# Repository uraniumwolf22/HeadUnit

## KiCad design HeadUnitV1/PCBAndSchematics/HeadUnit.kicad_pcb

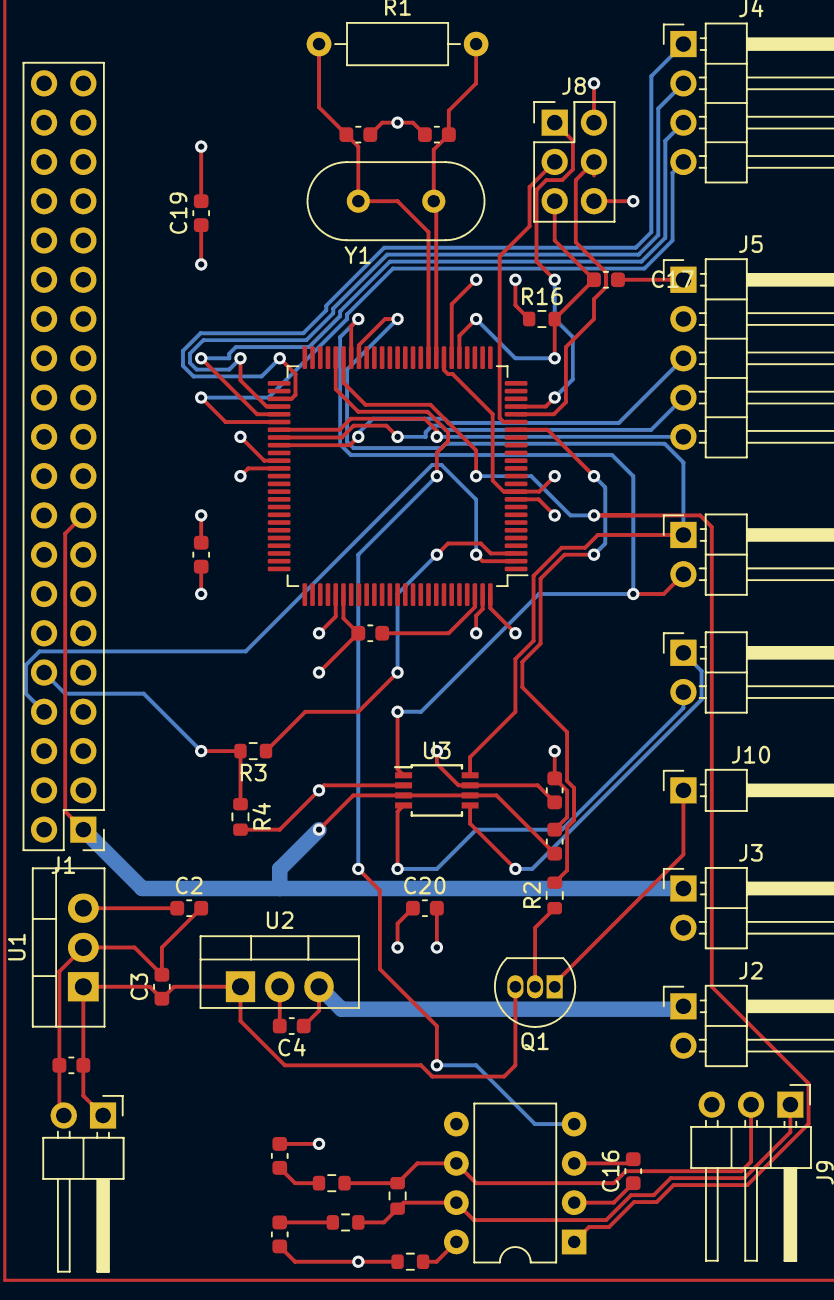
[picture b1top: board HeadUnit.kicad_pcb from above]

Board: 4 copper layers, 43 parts (0 on the bottom side), 36 nets.

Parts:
C1, C3: 0.33uF; C_0603_1608Metric
C2, C4, C5, C6, C16, C17: 0.1uF; C_0603_1608Metric
C9, C10: 22pf; C_0603_1608Metric
C14, C15: 560pF; C_0603_1608Metric
C18, C19, C20, C21: 0.1uf; C_0603_1608Metric
J1: Raspberry_Pi_2_3; PinHeader_2x20_P2.54mm_Vertical
J2: 5VOUT; PinHeader_1x02_P2.54mm_Horizontal
J3: 3V3OUT; PinHeader_1x02_P2.54mm_Horizontal
J4: MC_GPIO; PinHeader_1x04_P2.54mm_Horizontal
J5: ENC_CONN; PinHeader_1x05_P2.54mm_Horizontal
J6: I2C_LV; PinHeader_1x02_P2.54mm_Horizontal
J7: I2C_HV; PinHeader_1x02_P2.54mm_Horizontal
J8: AVR-ISP-6; PinHeader_2x03_P2.54mm_Vertical
J9: CAN_CONN; PinHeader_1x03_P2.54mm_Horizontal
J10: amp Conn; PinHeader_1x01_P2.54mm_Horizontal
J11: Conn_01x02_Pin; PinHeader_1x02_P2.54mm_Horizontal
Q1: 2N3904; TO-92_Inline
R1: 1M; R_Axial_DIN0207_L6.3mm_D2.5mm_P10.16mm_Horizontal
R2: 220; R_0603_1608Metric
R3: 510ohm; R_0603_1608Metric
R4: 1k; R_0603_1608Metric
R12: 120E; R_0603_1608Metric
R13, R14: 100E; R_0603_1608Metric
R15, R16: 4.7k; R_0603_1608Metric
U1, U2: LM7805_TO220; TO-220-3_Vertical
U3: TCA9406DC; TSSOP-8_3x3mm_P0.65mm
U5: MCP2551-I-P; DIP-8_W7.62mm
U6: ATmega2560-16A; TQFP-100_14x14mm_P0.5mm
Y1: 8Mhz; Crystal_HC49-4H_Vertical

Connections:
+3.3V: C5.1, J1.1 (3V3), J1.17 (3V3), J3.1, U3.3 (VCCA), U3.6 (OE)
+5V: C2.1, C6.2, C16.2, C19.2, C20.2, C21.2, J1.2 (5V), J1.4 (5V), J5.2, J8.2 (VCC), R16.1, U1.3 (VO), U3.7 (VCCB), U5.3 (VDD), U6.10 (VCC), U6.31 (VCC), U6.61 (VCC), U6.80 (VCC), U6.100 (AVCC)
+12V: C1.1, C3.1, J11.1, Q1.3 (C), U1.1 (VI), U2.1 (VI)
/5v_AUX: C4.1, J2.1, U2.3 (VO)
/AMP_CTRL: R2.2, U6.19 (PB0)
/AMP_SIG: J10.1, Q1.1 (E)
/CAN_H: J9.1, R12.1, R14.1, U5.7 (CANH)
/CAN_L: J9.2, R12.2, R13.1, U5.6 (CANL)
/CAN_RX: U5.1 (TXD), U6.45 (PD2)
/CAN_TX: U5.4 (RXD), U6.46 (PD3)
/ENC_CLK: J5.5, U6.57 (PC4)
/ENC_DT: J5.4, U6.58 (PC5)
/ENC_SW: J5.3, U6.59 (PC6)
/MEGA_GPIO_1: J4.1, U6.53 (PC0)
/MEGA_GPIO_2: J4.2, U6.54 (PC1)
/MEGA_GPIO_3: J4.3, U6.55 (PC2)
/MEGA_GPIO_4: J4.4, U6.56 (PC3)
/MEGA_MISO: J8.1 (MISO), U6.22 (PB3)
/MEGA_MOSI: J8.4 (MOSI), U6.21 (PB2)
/MEGA_RST: C17.1, J8.5 (~RST), R16.2, U6.30 (~RESET)
/MEGA_SCK: J8.3 (SCK), U6.20 (PB1)
/RX_LV: J1.8 (GPIO14/TXD), U6.2 (PE0)
/SCL_HV: J7.1, U3.8 (SCL_B), U6.43 (PD0)
/SCL_LV: J6.1, U3.5 (SCL_A)
/SDA_HV: J7.2, U3.1 (SDA_B), U6.44 (PD1)
/SDA_LV: J6.2, U3.4 (SDA_A)
/TX_HV: R3.1, U6.3 (PE1)
/TX_LV: J1.10 (GPIO15/RXD), R3.2, R4.1
/XTAL1: C10.1, R1.1, U6.34 (XTAL1), Y1.2
/XTAL2: C9.1, R1.2, U6.33 (XTAL2), Y1.1
GND: C1.2, C2.2, C3.2, C4.2, C5.2, C6.1, C9.2, C10.2, C14.2, C15.2, C16.1, C17.2, C18.1, C19.1, C20.1, C21.1, J1.6 (GND), J1.9 (GND), J1.14 (GND), J1.20 (GND), J1.25 (GND), J1.30 (GND), J1.34 (GND), J1.39 (GND), J2.2, J3.2, J5.1, J8.6 (GND), J9.3, J11.2, R4.2, R15.2, U1.2 (GND), U2.2 (GND), U3.2 (GND), U5.2 (VSS), U6.11 (GND), U6.32 (GND), U6.62 (GND), U6.81 (GND), U6.99 (GND)
unnamed: C14.1, R13.2
unnamed: C15.1, R14.2
unnamed: Q1.2 (B), R2.1
unnamed: R15.1, U5.8 (Rs)
unnamed: C18.2, U6.98 (AREF)

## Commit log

2023-07-22 FolderStructure
    Corrected folder structure
2023-07-22 Comments
    just a lil guy making some comments
2023-07-22 invertmask
2023-07-22 Unify variable style
2023-07-23 Update HUFirmware.ino
    Fixed SerialBuff variable and Moved serial functions to outside main loop
2023-07-23 debug mode 100
2023-07-23 Preliminary input logic
2023-07-23 Placeholder draw functions
2023-07-23 Set menu cursor index
2023-07-23 Fix compile errors
2023-07-23 Set orientation
2023-07-23 Selection overlay fix
2023-07-23 Fixes
2023-07-23 Fix Statmenu
2023-07-23 Improve selection overlay
2023-07-24 Added Schematic Files to Repo
2023-07-24 Added basic volume control
2023-07-24 Delete RPI_Services directory
    Removed due to bad permission
2023-07-25 Read and write functions
2023-07-25 Add obdII scripts
2024-06-03 MovedOldFiles
2024-06-03 Added main firmware file to branch
2024-06-04 Updating permissions
